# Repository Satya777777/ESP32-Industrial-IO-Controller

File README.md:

# ESP32 Industrial I/O Controller

A custom 4-layer ESP32-based industrial I/O controller designed in KiCad.

## Features

- ESP32-WROOM-32E
- 24 V input
- 0–10 V analog input
- 4–20 mA analog input
- RS485 communication
- USB-C programming/debugging
- 24 V relay output
- 5 V buck converter
- 3.3 V regulation
- 4-layer PCB
- Dedicated GND plane

## System Architecture

## PCB

## Documentation

- [Datasheet & User Manual](docs/ESP32_Industrial_IO_Controller_Datasheet_User_Manual.pdf)
- [Design Process & Engineering Record](docs/ESP32_Industrial_IO_Controller_Design_Process.pdf)

## Hardware

- KiCad schematic
- KiCad PCB
- Gerber files
- Drill files

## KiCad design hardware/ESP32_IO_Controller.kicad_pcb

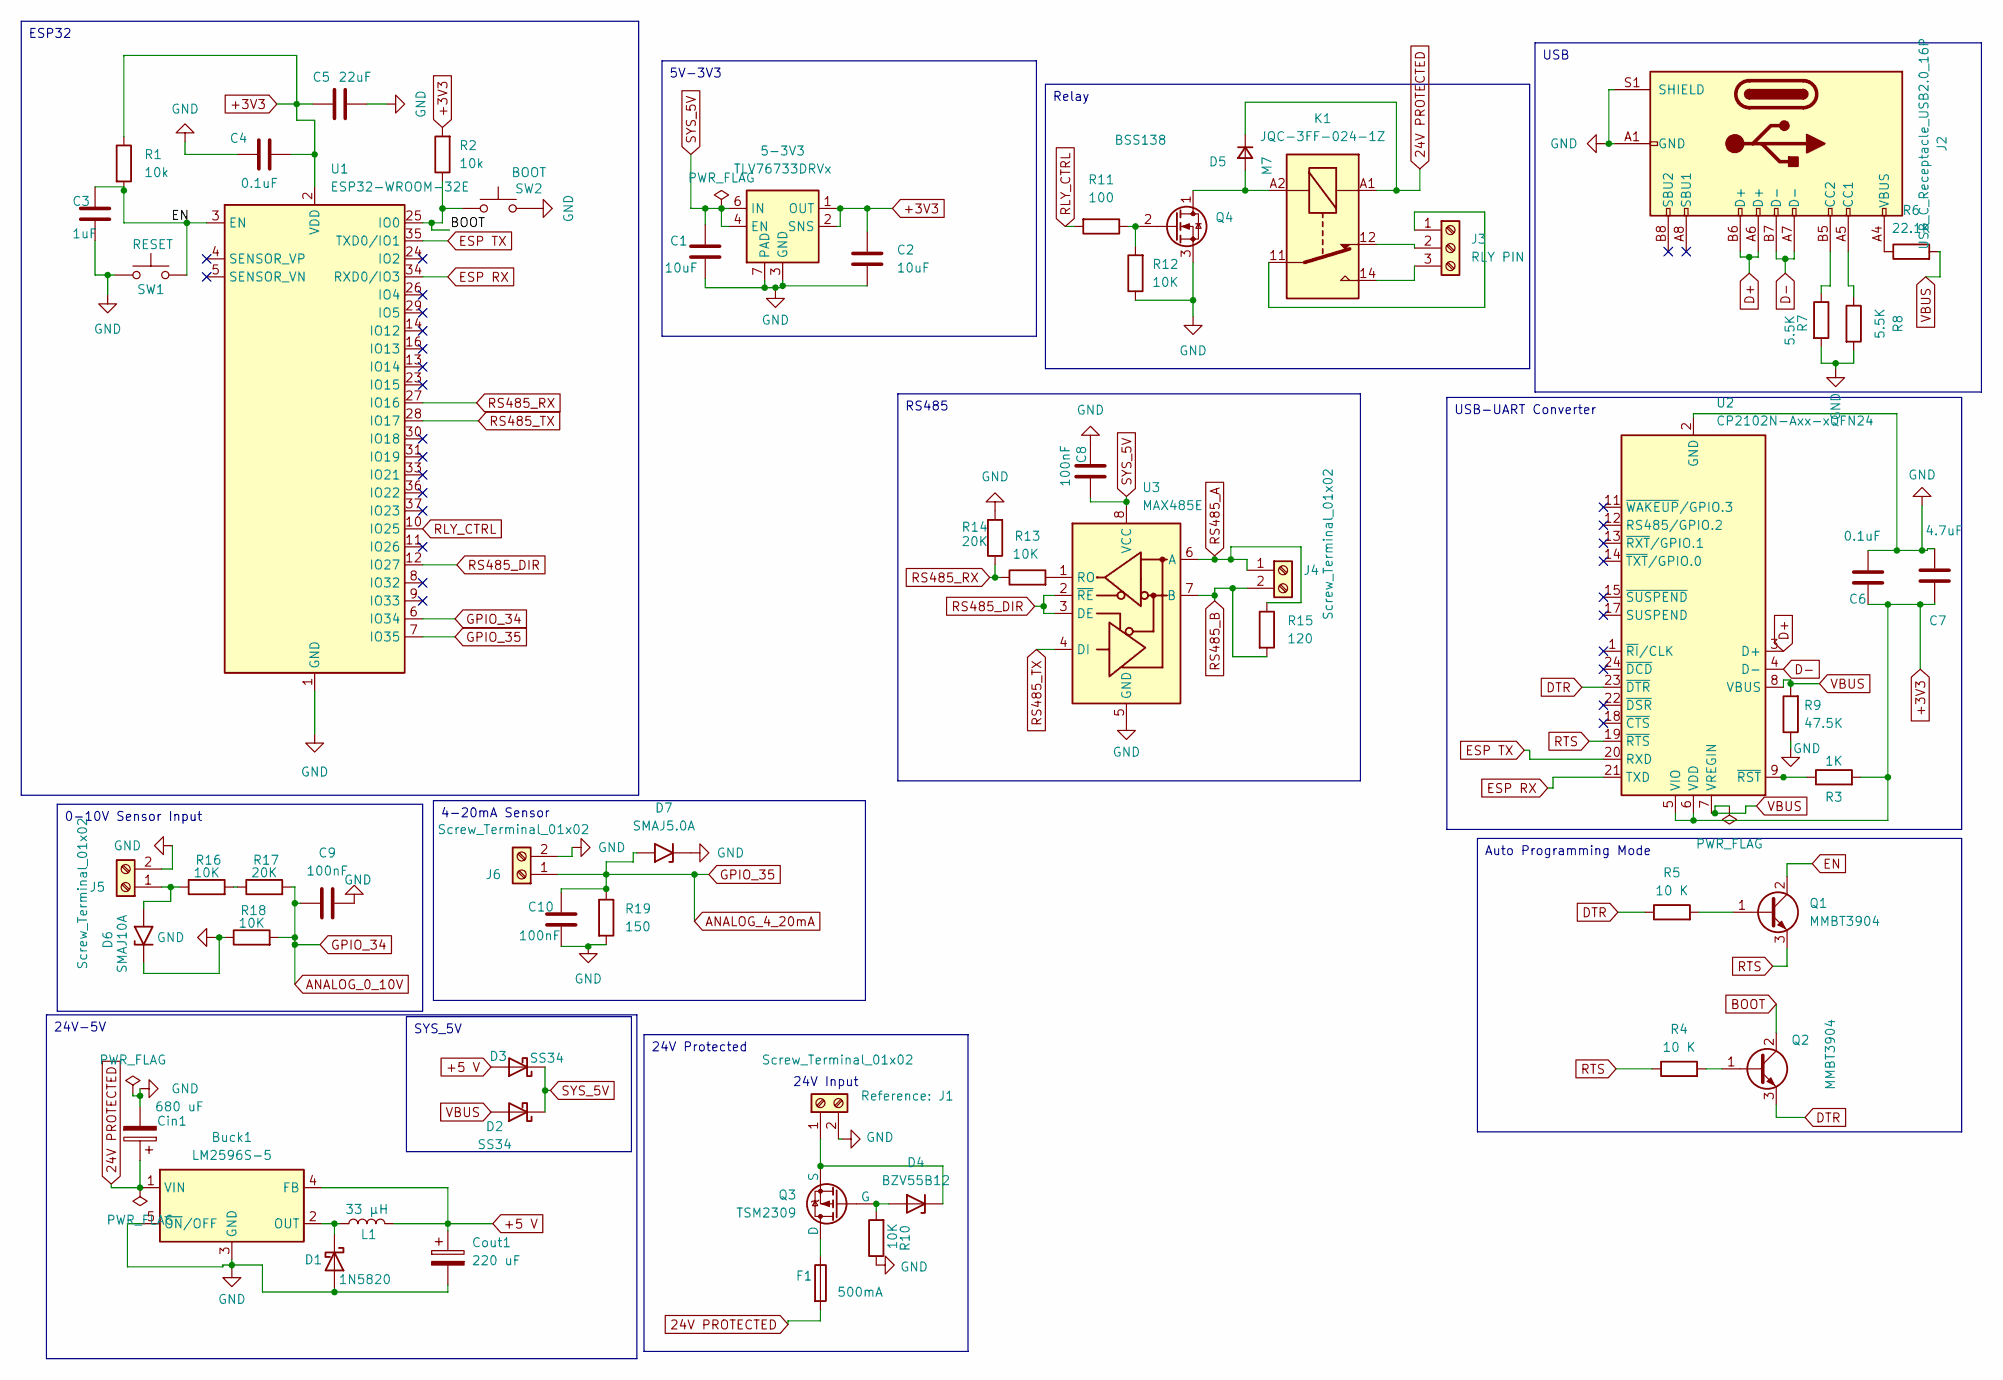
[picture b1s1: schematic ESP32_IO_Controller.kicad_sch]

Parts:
5-3V3: TLV76733DRVx; WSON-6-1EP_2x2mm_P0.65mm_EP1x1.6mm_ThermalVias
Buck1: LM2596S-5; TO-263-5_TabPin3
C1: 10uF; CP_Radial_D12.5mm_P5.00mm
C2: 10uF; C_1206_3216Metric
C3: 1uF; C_0805_2012Metric
C4, C6: 0.1uF; C_0603_1608Metric
C5: 22uF; C_1206_3216Metric
C7: 4.7uF; C_0805_2012Metric
C8, C9: 100nF; C_0603_1608Metric
C10: 100nF; C_0805_2012Metric
Cin1: 680 uF; CP_Radial_D12.5mm_P5.00mm
Cout1: 220 uF; CP_Radial_D8.0mm_P3.50mm
D1: 1N5820; D_DO-201AD_P15.24mm_Horizontal
D2, D3: SS34; D_SMA
D4: BZV55B12; D_MiniMELF
D5: M7; D_SMA
D6: SMAJ10A; D_SMA
D7: SMAJ5.0A; D_SMA
F1: 500mA; Fuseholder_Clip-5x20mm_Schurter_CQM_Inline_P20.60x5.00mm_D1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
J1, J4, J5, J6: Screw_Terminal_01x02; TerminalBlock_Phoenix_MKDS-3-2-5.08_1x02_P5.08mm_Horizontal
J2: USB_C_Receptacle_USB2.0_16P; USB_C_Receptacle_HRO_TYPE-C-31-M-12
J3: RLY PIN; TerminalBlock_Phoenix_MKDS-3-3-5.08_1x03_P5.08mm_Horizontal
K1: JQC-3FF-024-1Z; Relay_SPDT_Hongfa_JQC-3FF_0XX-1Z
L1: 33 µH; L_Bourns-SRN1060
Q1, Q2: MMBT3904; SOT-23
Q3: TSM2309; SOT-23
Q4: BSS138; SOT-23
R1, R2: 10k; R_0805_2012Metric
R3: 1K; R_0805_2012Metric
R4, R5: 10 K; R_0805_2012Metric
R6: 22.1K; R_0805_2012Metric
R7, R8: 5.5K; R_0805_2012Metric
R9: 47.5K; R_0805_2012Metric
R10, R12, R13, R16, R18: 10K; R_0805_2012Metric
R11: 100; R_0805_2012Metric
R14, R17: 20K; R_0805_2012Metric
R15: 120; R_0805_2012Metric
R19: 150; R_0805_2012Metric
SW1: RESET; SW_PUSH_6mm
SW2: BOOT; SW_PUSH_6mm
U1: ESP32-WROOM-32E; ESP32-WROOM-32D
U2: CP2102N-Axx-xQFN24; QFN-24-1EP_4x4mm_P0.5mm_EP2.6x2.6mm
U3: MAX485E; SOIC-8_3.9x4.9mm_P1.27mm

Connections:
24V PROTECTED: Buck1.1 (VIN), Cin1.1, D5.1 (K), F1.2, K1.A1
+3V3: 5-3V3.1 (OUT), 5-3V3.2 (SNS), C2.1, C4.2, C5.1, C6.1, C7.1, R1.1, R2.2, R3.2, U1.2 (VDD), U2.5 (VIO), U2.6 (VDD); also elsewhere on the board
+5 V: Buck1.4 (FB), Cout1.1, D3.2 (A), L1.2
ANALOG_0_10V: C9.1, R17.2, R18.2, U1.6 (IO34)
ANALOG_4_20mA: C10.1, D7.2 (A2), J6.1 (4-20mA), R19.1, U1.7 (IO35)
BOOT: Q2.2 (C), R2.1, SW2.1, U1.25 (IO0)
D+: J2.A6 (D+), J2.B6 (D+), U2.3 (D+)
D-: J2.A7 (D-), J2.B7 (D-), U2.4 (D-)
DTR: Q2.3 (E), R5.1, U2.23 (~DTR)
EN: C3.2, Q1.2 (C), R1.2, SW1.2, U1.3 (EN)
ESP RX: U1.34 (RXD0/IO3), U2.21 (TXD)
ESP TX: U1.35 (TXD0/IO1), U2.20 (RXD)
GND: 5-3V3.3 (GND), 5-3V3.5 (GND), 5-3V3.7 (PAD), Buck1.3 (GND), Buck1.5 (~ON/OFF), C1.2, C2.2, C3.1, C4.1, C5.2, C6.2, C7.2, C8.1, C9.2, C10.2, Cin1.2, Cout1.2, D1.2 (A), D6.1 (A1), D7.1 (A1), J1.2 (GND), J2.A1 (GND), J2.A12 (GND), J2.B1 (GND), J2.B12 (GND), J2.S1 (SHIELD), J5.2 (GND), J6.2 (GND), Q4.3 (S), R7.2, R8.2, R9.1, R10.1, R12.1, R14.2, R18.1, R19.2, SW1.1, SW2.2, U1.1 (GND), U1.15 (GND), U1.38 (GND), U1.39 (GND), U2.2 (GND), U2.25 (GND), U3.5 (GND); also elsewhere on the board
unnamed: Buck1.2 (OUT), D1.1 (K), L1.1
unnamed: D4.2 (A), Q3.2 (G), R10.2
unnamed: D4.1 (K), J1.1 (24V), Q3.3 (S)
unnamed: D5.2 (A), K1.A2, Q4.1 (D)
unnamed: D6.2 (A2), J5.1 (0-10_V), R16.1
unnamed: J2.A5 (CC1), R8.1
unnamed: J2.B5 (CC2), R7.1
unnamed: J2.A4 (VBUS), J2.A9 (VBUS), J2.B4 (VBUS), J2.B9 (VBUS), R6.1
unnamed: J3.1 (COM), K1.11
unnamed: J3.2 (NC), K1.12
unnamed: J3.3 (NO), K1.14
unnamed: Q1.1 (B), R5.2
unnamed: Q2.1 (B), R4.2
unnamed: F1.1, Q3.1 (D)
unnamed: Q4.2 (G), R11.1, R12.2
unnamed: R16.2, R17.1
unnamed: R3.1, U2.9 (~RST)
unnamed: R13.2, U3.1 (RO)
RLY_CTRL: R11.2, U1.10 (IO25)
RS485_A: J4.1 (A), R15.1, U3.6 (A)
RS485_B: J4.2 (B), R15.2, U3.7 (B)
RS485_DIR: U1.12 (IO27), U3.2 (~RE), U3.3 (DE)
RS485_RX: R13.1, R14.1, U1.27 (IO16)
RS485_TX: U1.28 (IO17), U3.4 (DI)
RTS: Q1.3 (E), R4.1, U2.19 (~RTS)
SYS_5V: 5-3V3.4 (EN), 5-3V3.6 (IN), C1.1, C8.2, D2.1 (K), D3.1 (K), U3.8 (VCC); also elsewhere on the board
VBUS: D2.2 (A), R6.2, R9.2, U2.7 (VREGIN), U2.8 (VBUS)

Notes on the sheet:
24V Input
USB-UART Converter
0-10V Sensor Input
Auto Programming Mode
24V-5V
4-20mA Sensor
ESP32
SYS_5V
Relay
USB
24V Protected
RS485
5V-3V3

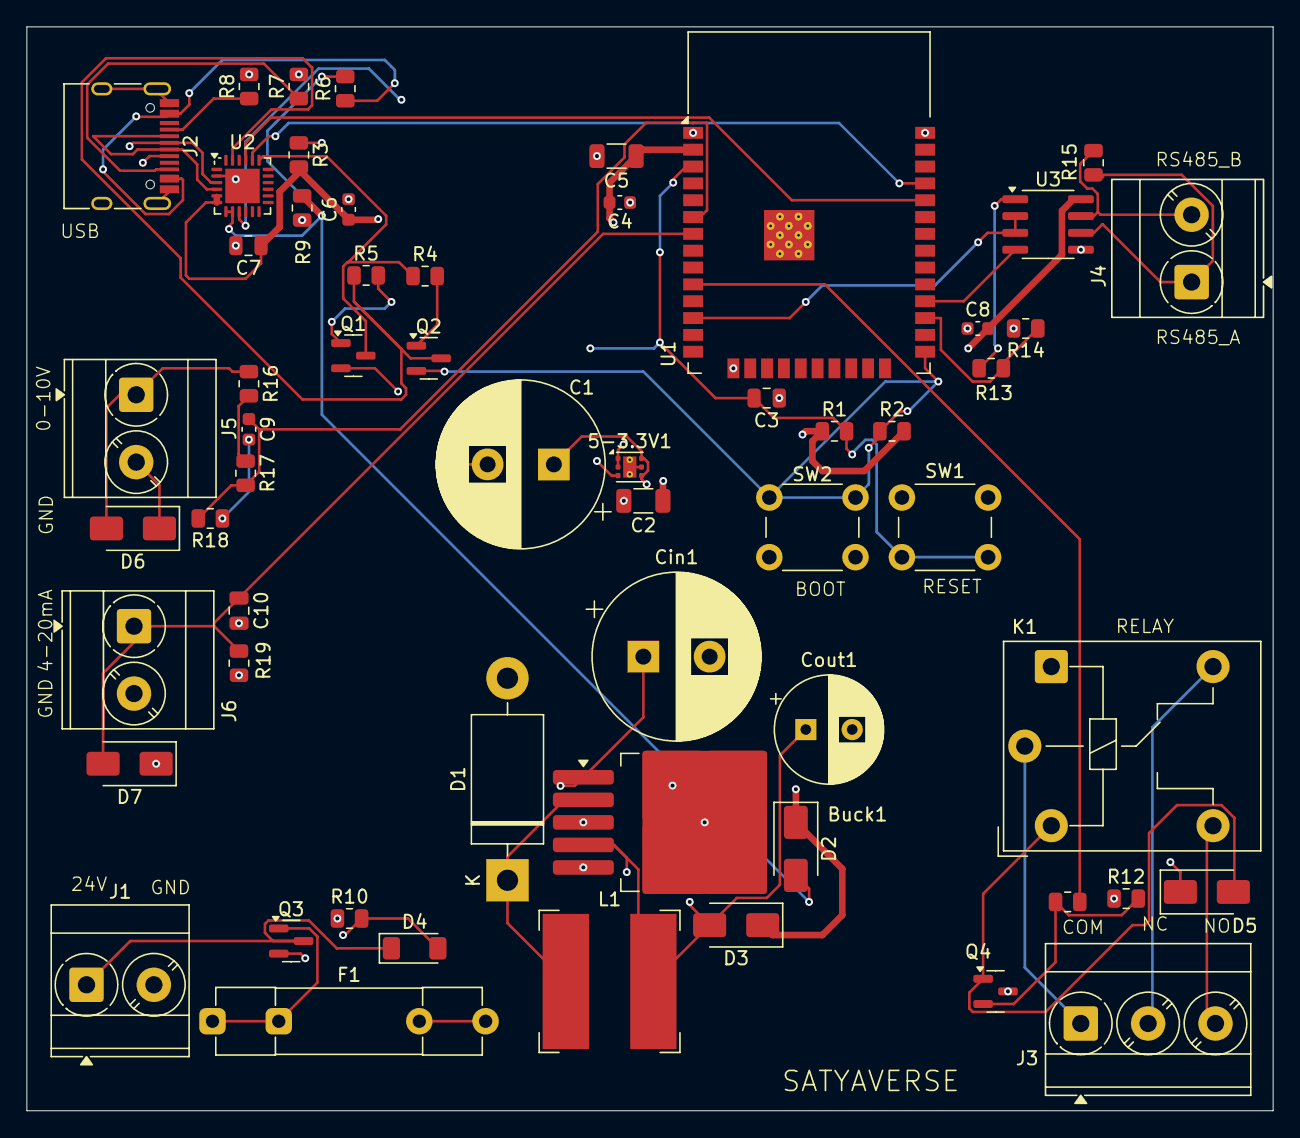
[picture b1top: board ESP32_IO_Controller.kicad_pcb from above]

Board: 4 copper layers, 94.0 x 81.8 mm, 58 parts (0 on the bottom side), 40 nets.

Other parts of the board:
5-3.3V1: TLV76733DRVx; WSON-6-1EP_2x2mm_P0.65mm_EP1x1.6mm_ThermalVias

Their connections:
+3V3: 5-3.3V1.1 (OUT), 5-3.3V1.2 (SNS); also elsewhere on the board
GND: 5-3.3V1.3 (GND), 5-3.3V1.5 (GND), 5-3.3V1.7 (PAD); also elsewhere on the board
SYS_5V: 5-3.3V1.4 (EN), 5-3.3V1.6 (IN); also elsewhere on the board
